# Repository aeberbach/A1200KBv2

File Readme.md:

A few years ago I made my first Amiga 1200 mechanical keyboard. I did not know at the time about any other efforts that might be underway so I just went ahead and did it. It turned out well and a lot of people built them. Still, there is always a temptation to try and improve something. I was never really happy about the mounting system and the 9U spacebar was a problem, even more so than finding the keycaps that match the Amiga key sizes because modern keyboards went in a different direction.

So here is version 2. At the time of the last keyboard, low-profile keyswitches existed but were hard to find and often could not use MX-stem caps, now it is easier. I'm typing this with a Nuphy Air75 v2 with "Gateron x Nuphy Moss" KS-33 switches and the feel is amazing. There is a lighter variant "Wisteria" and a regular brown tactile option. Blue (clicky) and several variants of linear including red are available too. These switches use a different footprint to standard MX so the PCB had to be redone.

The low profile switches do not come in a 5-pin PCB mount version so a plate is essential. While laser-cut would be amazing I don't have a laser cutter, also that would not be 3-dimensional and would not leave space for the stabilizer wires. To keep it printable on common 3D printers there are multiple pieces to print. I have used eSun matte PLA, a good opaque material that is a good match for an A1200.net case in white or black. The stabilizers mount to the plates, the holes in the PCB underneath are only for clearance. These plates keep the keyswitches perfectly straight during assembly, improve keyboard stiffness, dampen sound and make for a better appearance.

Under the old keyboard a 10x3mm aluminium bar was used to stiffen the whole assembly, running from one side of the case to another sitting on 3d-printed mounts. I want to move that out of the way of expansions under the keyboard. I never noticed a problem with a TF1230 but with a larger accelerator having a heatsink it might be. There is plenty of room for a PiStorm32-lite, by far the fastest and most cost-effective accelerator today.

One thing that hasn't been done is to source a Caps Lock key with a window for the LED. The LED mount is still there and you can put a LED under the switch but I don't know where you can get a windowed keycap for it. The LED section of this keyboard includes a circuit where it will light an alternate LED for power when Caps Lock is active. My keybaord has a green LED for power but that changes to blue when Caps Lock is activated.

If you don't want to use the LED function of this keyboard you can just snip away the top right of the PCB and use the original Amiga 1200 LED PCB. In that case don't bother with LEDs, capacitor, resistors or the inverter chip.

Requirements:
- one PCB (see the 'fab' folder for gerber files, ready to build)
- 96 Gateron KS-33 keyswitches
- 5 Gateron 2U plate-mount low-profile stabilizers
- 1 more Gateron low-profile stabilizer to disassemble - bend your own wire from 1.0mm music wire, available from hobby stores.
- 0805 LEDs: red, green, yellow/orange and blue (or whatever colors you like for the various functions)
- 0805 current-limiting resistor for each LED. Choose a value not less than 300 ohms. If your LEDs are too bright you can use higher values. I found that 500-1k ohms is fine. Your LEDs may vary.
- 0.1uF 0805 decoupling capacitor
- SN74LVC2G04DBVR dual inverter (available Mouser electronics)
- 5-pin dupont housing, pins and ribbon cable to connect LED section to Amiga
- one FFC connector, 32-way RA 1.25mm pitch. Molex 52044-3245 (available Mouser Electronics) or look on AliExpress.
- one FFC ribbon cable, 31-way. Cut one connector from Molex 15168-0400 (available Mouser Electronics) or look on AliExpress.
- Printed left and right plates to house stabilizers and switches on top of PCB (STLs in 3dprint folder)
- Printed left, right and bottom mounts to secure the keyboard in your case (STLs in 3dprint folder)
- various M3 bolts or plastic rivets for assembly
- 96 Amiga keycaps: user Steveed on Amibay recently sorted this out with Signature Plastics and they are perfect. Seems expensive? Not until you spend hours looking for and buying various sets and never end up with a full set. 
 
The cost of all this varies with the cost of PCB manufacture, keyswitches and stabilizers and of course the keycaps. As a very rough guide expect to pay *no less* than about:
- PCB $20
- keyswitches $40
- stabilizers $20
- LEDs and other components $2
- FFC connector and cable $8
- 3D printed parts $10

And assembly will take at least three hours. That's just under $100 in parts alone and does not even count a quality set of keycaps at around $150. (But if you weren't slightly obsessed you probably wouldn't have an Amiga in 2024.)

The license for this keyboard is non-commercial. However if a person has ordered the minimum of 5 PCBs from one of the usual places and wants to offer the extras for sale at near cost that is reasonable.

Thanks to Steveed (Amibay) and to everyone that has supported this project. 

License: CC-BY-NC-SA 4.0

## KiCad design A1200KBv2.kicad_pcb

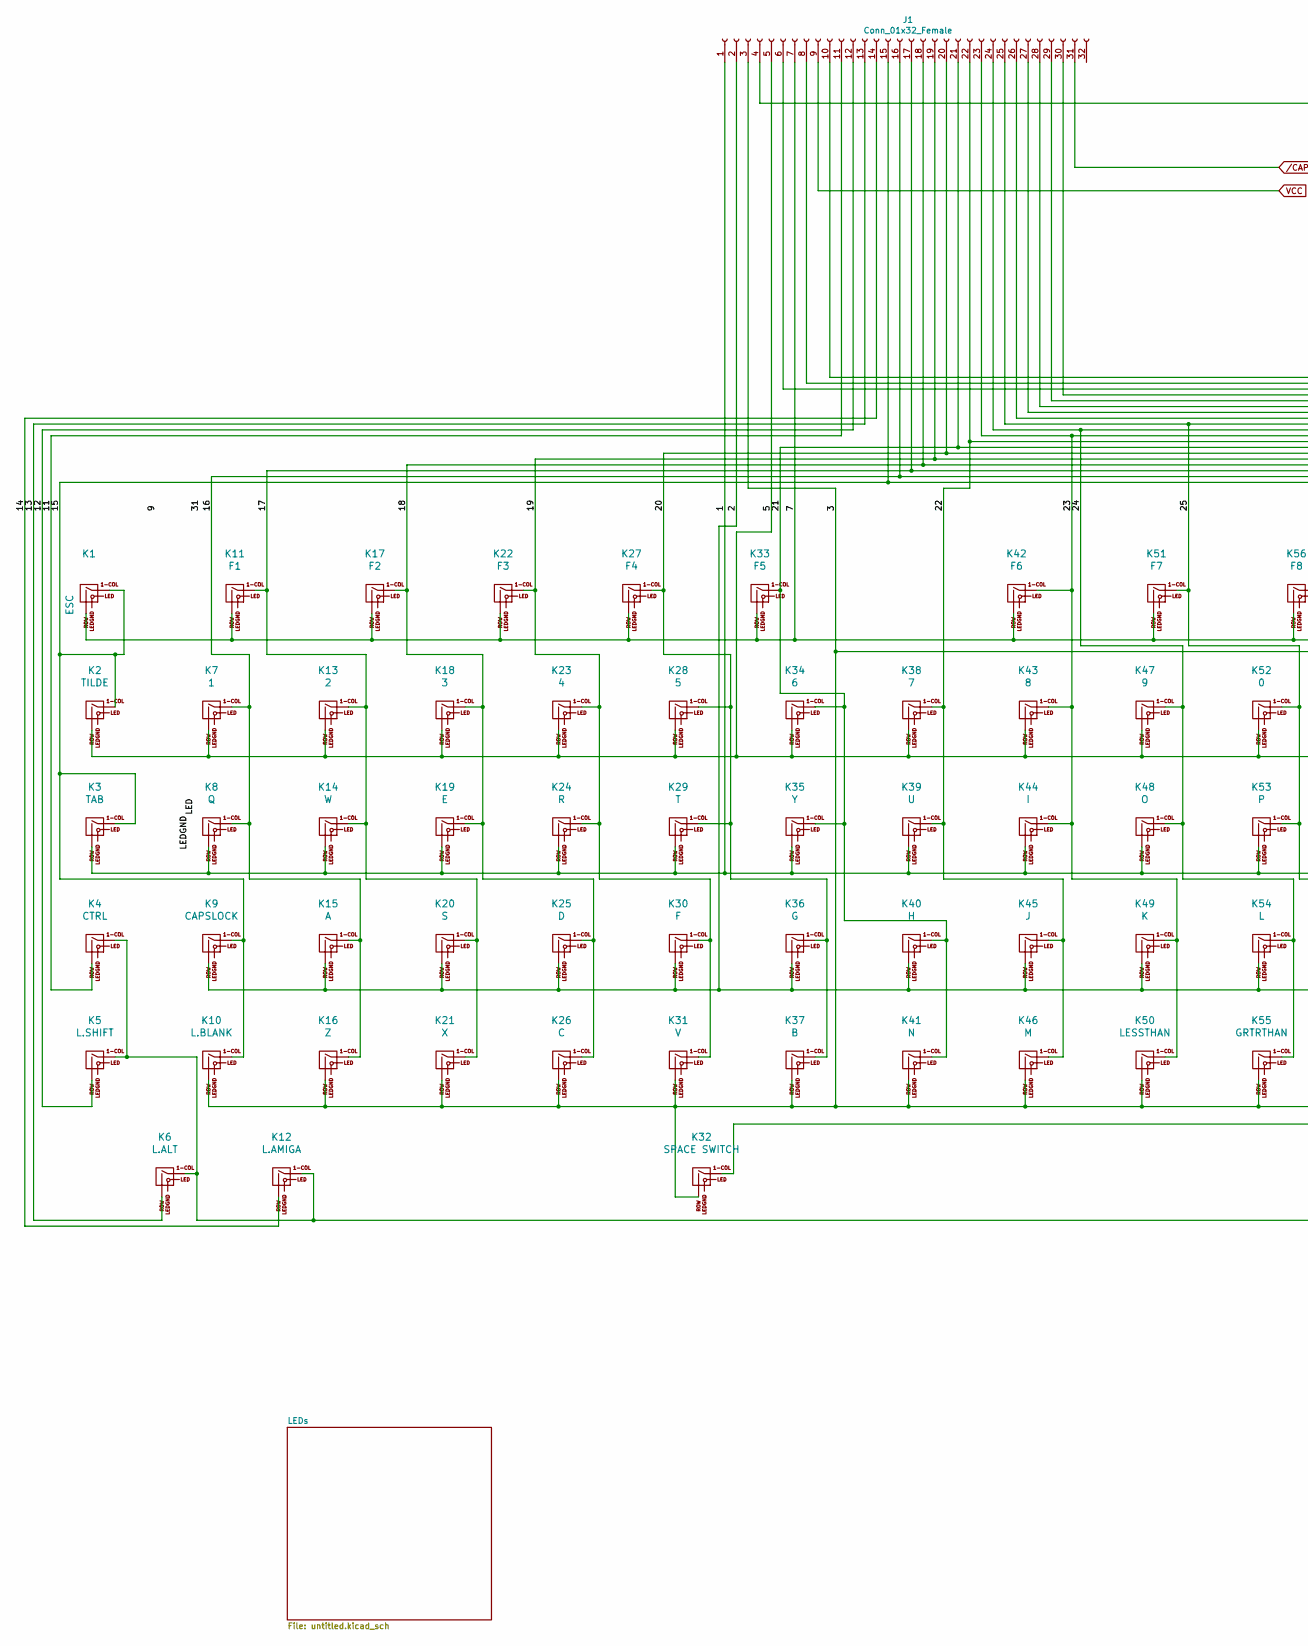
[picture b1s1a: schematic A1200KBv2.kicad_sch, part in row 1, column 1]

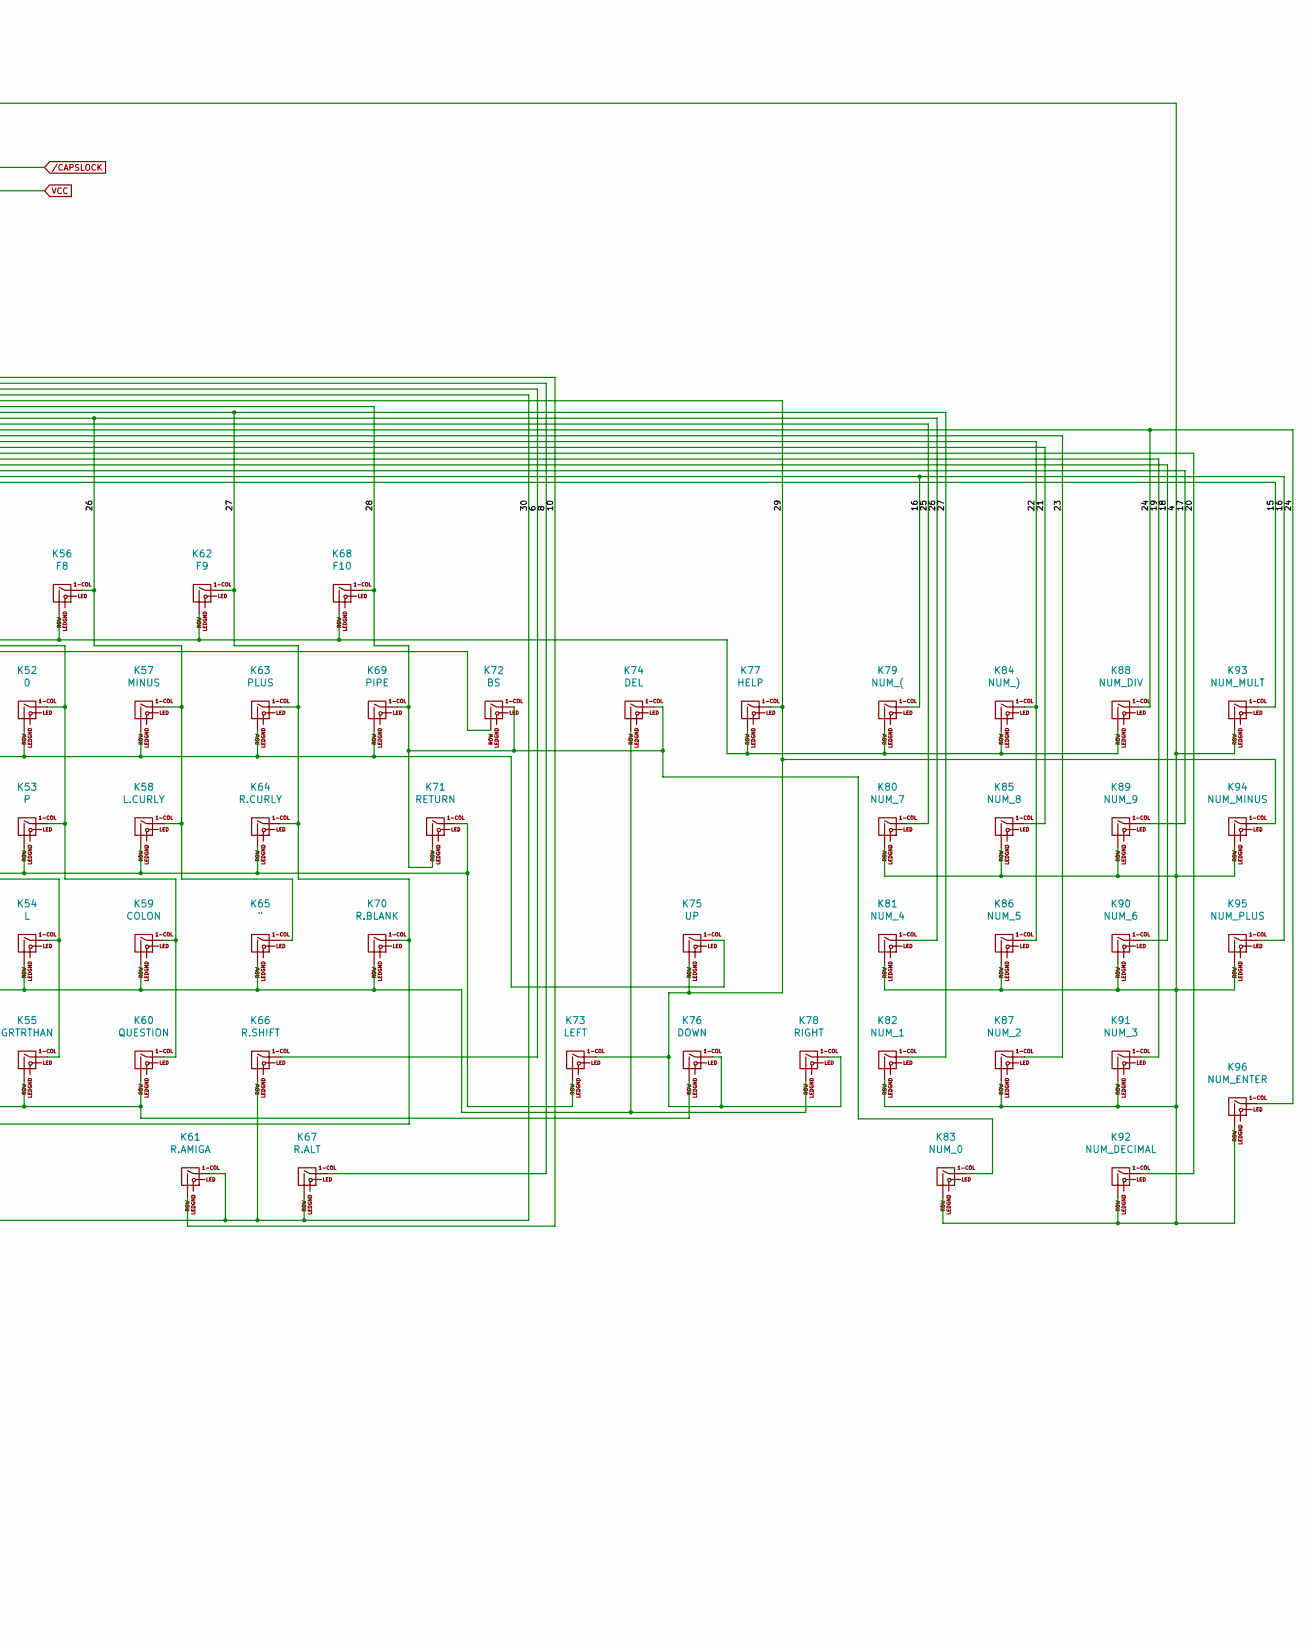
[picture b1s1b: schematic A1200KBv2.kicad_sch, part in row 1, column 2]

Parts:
J1: Conn_01x32_Female; FFC-1.25mm-RA-5204403245
K1: ESC; Gateron-KS33-Solderable-1U
K2: TILDE; Gateron-KS33-Solderable-1.5U
K3: TAB; KS-33-2U-stabilizer
K4: CTRL; Gateron-KS33-Solderable-1.25U
K5: L.SHIFT; Gateron-KS33-Solderable-1.75U
K6: L.ALT; Gateron-KS33-Solderable-1.25U
K7: 1; Gateron-KS33-Solderable-1U
K8: Q; Gateron-KS33-Solderable-1U
K9: CAPSLOCK; Gateron-KS33-Solderable-1U
K10: L.BLANK; Gateron-KS33-Solderable-1U
K11: F1; Gateron-KS33-Solderable-1.25U
K12: L.AMIGA; Gateron-KS33-Solderable-1.25U
K13: 2; Gateron-KS33-Solderable-1U
K14: W; Gateron-KS33-Solderable-1U
K15: A; Gateron-KS33-Solderable-1U
K16: Z; Gateron-KS33-Solderable-1U
K17: F2; Gateron-KS33-Solderable-1.25U
K18: 3; Gateron-KS33-Solderable-1U
K19: E; Gateron-KS33-Solderable-1U
K20: S; Gateron-KS33-Solderable-1U
K21: X; Gateron-KS33-Solderable-1U
K22: F3; Gateron-KS33-Solderable-1.25U
K23: 4; Gateron-KS33-Solderable-1U
K24: R; Gateron-KS33-Solderable-1U
K25: D; Gateron-KS33-Solderable-1U
K26: C; Gateron-KS33-Solderable-1U
K27: F4; Gateron-KS33-Solderable-1.25U
K28: 5; Gateron-KS33-Solderable-1U
K29: T; Gateron-KS33-Solderable-1U
K30: F; Gateron-KS33-Solderable-1U
K31: V; Gateron-KS33-Solderable-1U
K32: SPACE SWITCH; KS-33-8U-space
K33: F5; Gateron-KS33-Solderable-1.25U
K34: 6; Gateron-KS33-Solderable-1U
K35: Y; Gateron-KS33-Solderable-1U
K36: G; Gateron-KS33-Solderable-1U
K37: B; Gateron-KS33-Solderable-1U
K38: 7; Gateron-KS33-Solderable-1U
K39: U; Gateron-KS33-Solderable-1U
K40: H; Gateron-KS33-Solderable-1U
K41: N; Gateron-KS33-Solderable-1U
K42: F6; Gateron-KS33-Solderable-1.25U
K43: 8; Gateron-KS33-Solderable-1U
K44: I; Gateron-KS33-Solderable-1U
K45: J; Gateron-KS33-Solderable-1U
K46: M; Gateron-KS33-Solderable-1U
K47: 9; Gateron-KS33-Solderable-1U
K48: O; Gateron-KS33-Solderable-1U
K49: K; Gateron-KS33-Solderable-1U
K50: LESSTHAN; Gateron-KS33-Solderable-1U
K51: F7; Gateron-KS33-Solderable-1.25U
K52: 0; Gateron-KS33-Solderable-1U
K53: P; Gateron-KS33-Solderable-1U
K54: L; Gateron-KS33-Solderable-1U
K55: GRTRTHAN; Gateron-KS33-Solderable-1U
K56: F8; Gateron-KS33-Solderable-1.25U
K57: MINUS; Gateron-KS33-Solderable-1U
K58: L.CURLY; Gateron-KS33-Solderable-1U
K59: COLON; Gateron-KS33-Solderable-1U
K60: QUESTION; Gateron-KS33-Solderable-1U
K61: R.AMIGA; Gateron-KS33-Solderable-1.25U
K62: F9; Gateron-KS33-Solderable-1.25U
K63: PLUS; Gateron-KS33-Solderable-1U
K64: R.CURLY; Gateron-KS33-Solderable-1U
K65: "; Gateron-KS33-Solderable-1U
K66: R.SHIFT; KS-33-2U-stabilizer
K67: R.ALT; Gateron-KS33-Solderable-1.25U
K68: F10; Gateron-KS33-Solderable-1.25U
K69: PIPE; Gateron-KS33-Solderable-1U
K70: R.BLANK; Gateron-KS33-Solderable-1U
K71: RETURN; KS-33-ISO-2U-stabilizer
K72: BS; Gateron-KS33-Solderable-1U
K73: LEFT; Gateron-KS33-Solderable-1U
K74: DEL; Gateron-KS33-Solderable-1.5U
K75: UP; Gateron-KS33-Solderable-1U
K76: DOWN; Gateron-KS33-Solderable-1U
K77: HELP; Gateron-KS33-Solderable-1.5U
K78: RIGHT; Gateron-KS33-Solderable-1U
K79: NUM_(; Gateron-KS33-Solderable-1U
K80: NUM_7; Gateron-KS33-Solderable-1U
K81: NUM_4; Gateron-KS33-Solderable-1U
K82: NUM_1; Gateron-KS33-Solderable-1U
K83: NUM_0; KS-33-2U-stabilizer
K84: NUM_); Gateron-KS33-Solderable-1U
K85: NUM_8; Gateron-KS33-Solderable-1U
K86: NUM_5; Gateron-KS33-Solderable-1U
K87: NUM_2; Gateron-KS33-Solderable-1U
K88: NUM_DIV; Gateron-KS33-Solderable-1U
K89: NUM_9; Gateron-KS33-Solderable-1U
K90: NUM_6; Gateron-KS33-Solderable-1U
K91: NUM_3; Gateron-KS33-Solderable-1U
K92: NUM_DECIMAL; Gateron-KS33-Solderable-1U
K93: NUM_MULT; Gateron-KS33-Solderable-1U
K94: NUM_MINUS; Gateron-KS33-Solderable-1U
K95: NUM_PLUS; Gateron-KS33-Solderable-1U
K96: NUM_ENTER; KS-33-2U-stabilizer

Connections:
/1: J1.1, K3.2 (ROW), K8.2 (ROW), K14.2 (ROW), K19.2 (ROW), K24.2 (ROW), K29.2 (ROW), K35.2 (ROW), K39.2 (ROW), K44.2 (ROW), K48.2 (ROW), K53.2 (ROW), K58.2 (ROW), K64.2 (ROW), K71.1 (COL), K73.2 (ROW)
/2: J1.2, K9.2 (ROW), K15.2 (ROW), K20.2 (ROW), K25.2 (ROW), K30.2 (ROW), K36.2 (ROW), K40.2 (ROW), K45.2 (ROW), K49.2 (ROW), K54.2 (ROW), K59.2 (ROW), K65.2 (ROW), K70.2 (ROW), K74.2 (ROW), K78.2 (ROW)
/3: J1.3, K10.2 (ROW), K16.2 (ROW), K21.2 (ROW), K26.2 (ROW), K31.2 (ROW), K32.2 (ROW), K37.2 (ROW), K41.2 (ROW), K46.2 (ROW), K50.2 (ROW), K55.2 (ROW), K60.2 (ROW), K72.2 (ROW), K76.2 (ROW)
/4: J1.4, K80.2 (ROW), K81.2 (ROW), K82.2 (ROW), K83.2 (ROW), K85.2 (ROW), K86.2 (ROW), K87.2 (ROW), K89.2 (ROW), K90.2 (ROW), K91.2 (ROW), K92.2 (ROW), K93.2 (ROW), K94.2 (ROW), K95.2 (ROW), K96.2 (ROW)
/5: J1.5, K2.2 (ROW), K7.2 (ROW), K13.2 (ROW), K18.2 (ROW), K23.2 (ROW), K28.2 (ROW), K34.2 (ROW), K38.2 (ROW), K43.2 (ROW), K47.2 (ROW), K52.2 (ROW), K57.2 (ROW), K63.2 (ROW), K69.2 (ROW), K75.1 (COL)
/6: J1.6, K66.1 (COL)
/7: J1.7, K1.2 (ROW), K11.2 (ROW), K17.2 (ROW), K22.2 (ROW), K27.2 (ROW), K33.2 (ROW), K42.2 (ROW), K51.2 (ROW), K56.2 (ROW), K62.2 (ROW), K68.2 (ROW), K77.2 (ROW), K79.2 (ROW), K84.2 (ROW), K88.2 (ROW)
/8: J1.8, K67.1 (COL)
/10: J1.10, K61.2 (ROW)
/11: J1.11, K4.2 (ROW)
/12: J1.12, K5.2 (ROW)
/13: J1.13, K6.2 (ROW)
/14: J1.14, K12.2 (ROW)
/15: J1.15, K1.1 (COL), K2.1 (COL), K3.1 (COL), K9.1 (COL), K10.1 (COL), K93.1 (COL)
/16: J1.16, K7.1 (COL), K8.1 (COL), K15.1 (COL), K16.1 (COL), K79.1 (COL), K95.1 (COL)
/17: J1.17, K11.1 (COL), K13.1 (COL), K14.1 (COL), K20.1 (COL), K21.1 (COL), K89.1 (COL)
/18: J1.18, K17.1 (COL), K18.1 (COL), K19.1 (COL), K25.1 (COL), K26.1 (COL), K90.1 (COL)
/19: J1.19, K22.1 (COL), K23.1 (COL), K24.1 (COL), K30.1 (COL), K31.1 (COL), K91.1 (COL)
/20: J1.20, K27.1 (COL), K28.1 (COL), K29.1 (COL), K36.1 (COL), K37.1 (COL), K92.1 (COL)
/21: J1.21, K33.1 (COL), K34.1 (COL), K35.1 (COL), K40.1 (COL), K41.1 (COL), K85.1 (COL)
/22: J1.22, K38.1 (COL), K39.1 (COL), K45.1 (COL), K46.1 (COL), K84.1 (COL), K86.1 (COL)
/23: J1.23, K42.1 (COL), K43.1 (COL), K44.1 (COL), K49.1 (COL), K50.1 (COL), K87.1 (COL)
/24: J1.24, K47.1 (COL), K48.1 (COL), K54.1 (COL), K55.1 (COL), K88.1 (COL), K96.1 (COL)
/25: J1.25, K51.1 (COL), K52.1 (COL), K53.1 (COL), K59.1 (COL), K60.1 (COL), K80.1 (COL)
/26: J1.26, K56.1 (COL), K57.1 (COL), K58.1 (COL), K65.1 (COL), K81.1 (COL)
/27: J1.27, K32.1 (COL), K62.1 (COL), K63.1 (COL), K64.1 (COL), K70.1 (COL), K82.1 (COL)
/28: J1.28, K68.1 (COL), K69.1 (COL), K71.2 (ROW), K72.1 (COL), K74.1 (COL), K83.1 (COL)
/29: J1.29, K73.1 (COL), K75.2 (ROW), K76.1 (COL), K77.1 (COL), K78.1 (COL), K94.1 (COL)
/30: J1.30, K4.1 (COL), K5.1 (COL), K6.1 (COL), K12.1 (COL), K61.1 (COL), K66.2 (ROW), K67.2 (ROW)
VCC: J1.9; also elsewhere on the board
/CAPSLOCK: J1.31; also elsewhere on the board

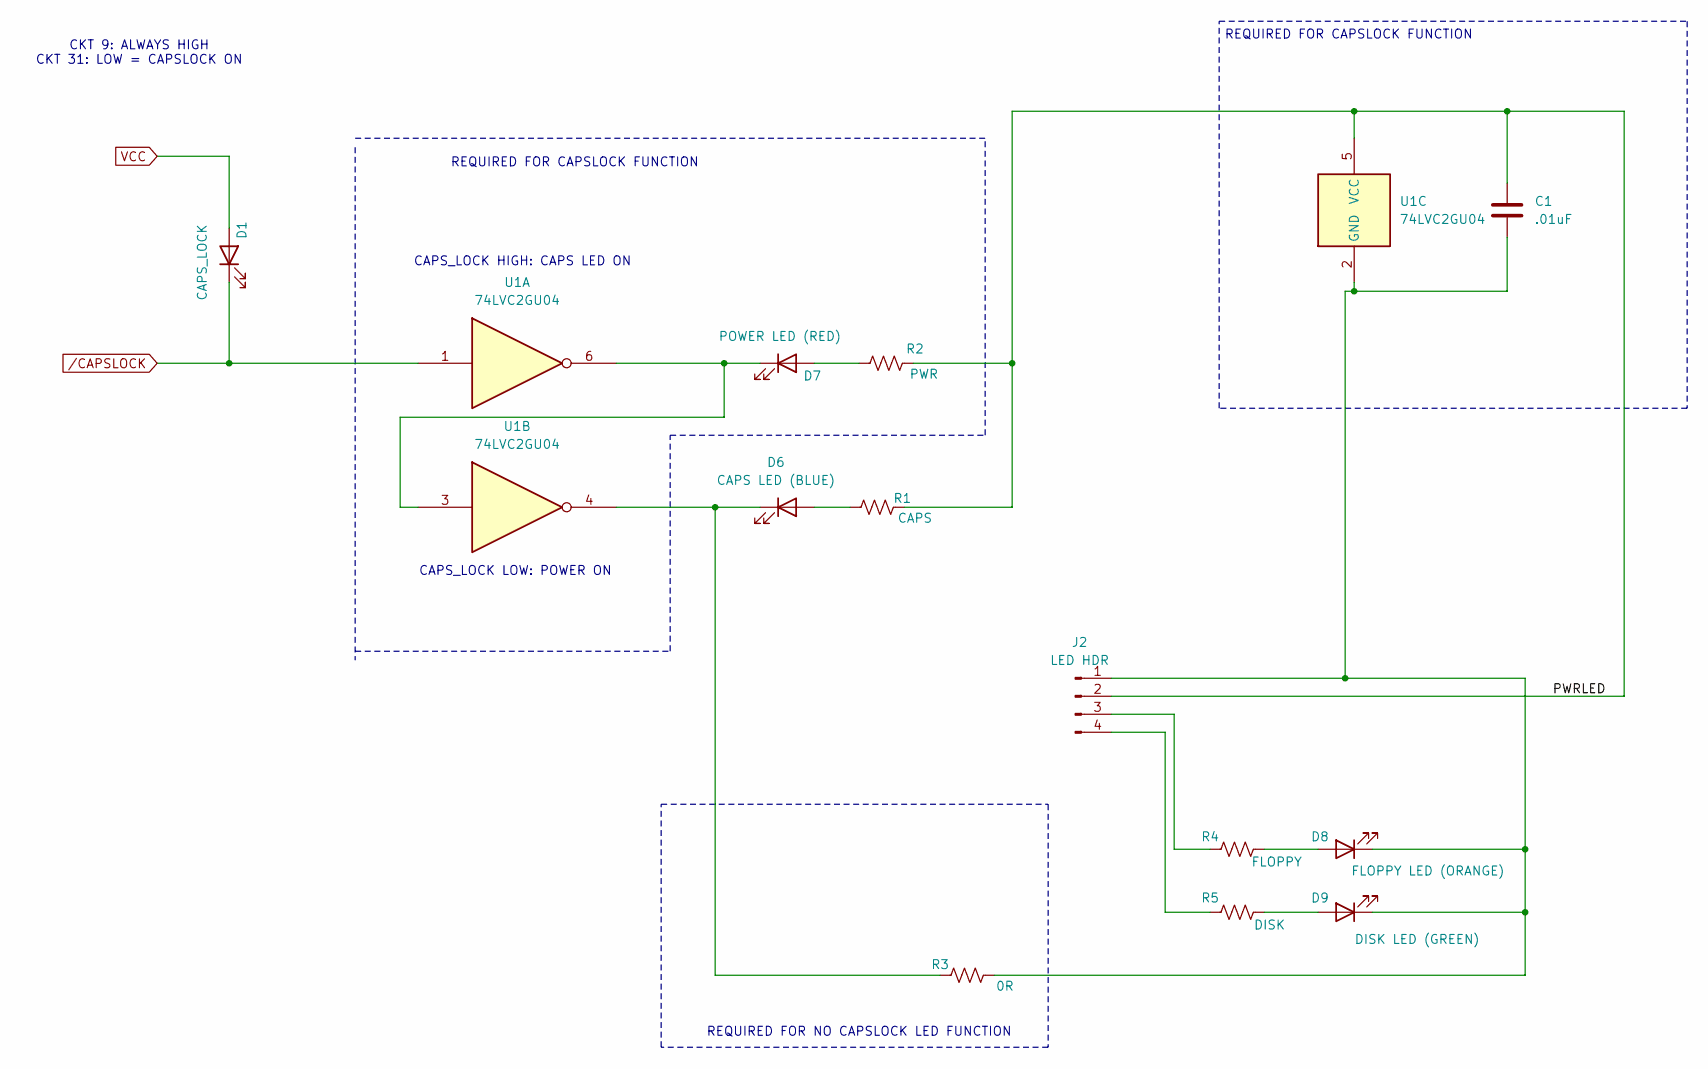
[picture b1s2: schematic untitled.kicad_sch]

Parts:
C1: .01uF; C_0805_2012Metric_Pad1.18x1.45mm_HandSolder
D1: CAPS_LOCK; LED_0805_2012Metric
D6: CAPS LED (BLUE); LED_0805_2012Metric
D7: POWER LED (RED); LED_0805_2012Metric
D8: FLOPPY LED (ORANGE); LED_0805_2012Metric
D9: DISK LED (GREEN); LED_0805_2012Metric
J2: LED HDR; PinHeader_1x04_P2.54mm_Vertical
R1: CAPS; R_0805_2012Metric_Pad1.20x1.40mm_HandSolder
R2: PWR; R_0805_2012Metric_Pad1.20x1.40mm_HandSolder
R3: 0R; R_0805_2012Metric_Pad1.20x1.40mm_HandSolder
R4: FLOPPY; R_0805_2012Metric_Pad1.20x1.40mm_HandSolder
R5: DISK; R_0805_2012Metric_Pad1.20x1.40mm_HandSolder
U1: 74LVC2GU04; SOT-23-6

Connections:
/LEDs/PWRLED: C1.1, J2.2, R1.2, R2.2, U1.5 (VCC)
unnamed: D6.2 (A), R1.1
unnamed: D6.1 (K), R3.1, U1.4
unnamed: D7.2 (A), R2.1
unnamed: D7.1 (K), U1.3, U1.6
unnamed: D8.2 (A), R4.2
unnamed: C1.2, D8.1 (K), D9.1 (K), J2.1, R3.2, U1.2 (GND)
unnamed: D9.2 (A), R5.2
unnamed: J2.3, R4.1
unnamed: J2.4, R5.1
VCC: D1.2 (A); also elsewhere on the board
/CAPSLOCK: D1.1 (K), U1.1; also elsewhere on the board

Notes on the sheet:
CAPS_LOCK LOW: POWER ON
CKT 9: ALWAYS HIGH CKT 31: LOW = CAPSLOCK ON
REQUIRED FOR CAPSLOCK FUNCTION
CAPS_LOCK HIGH: CAPS LED ON
REQUIRED FOR NO CAPSLOCK LED FUNCTION

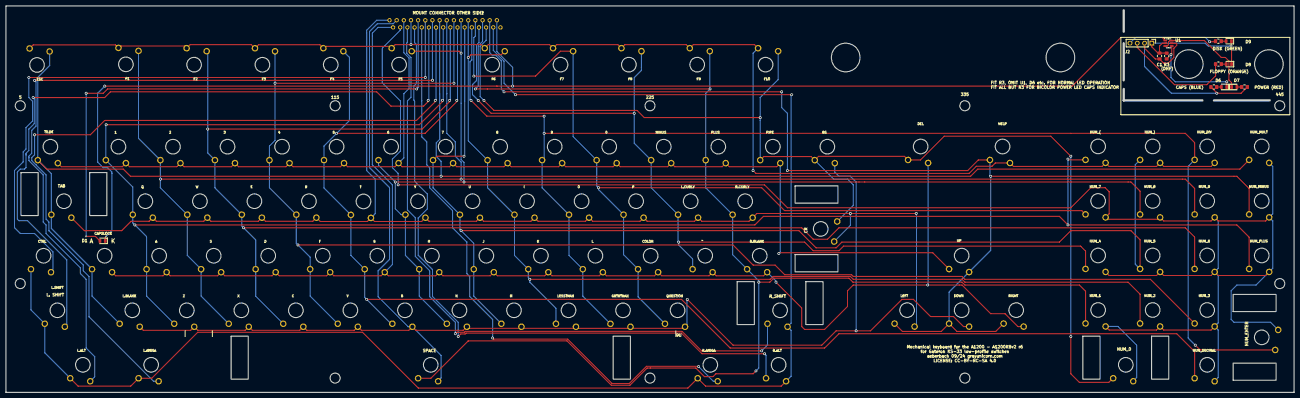
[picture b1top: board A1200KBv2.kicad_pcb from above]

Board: 2 copper layers, 450.0 x 135.0 mm, 110 parts (1 on the bottom side), 41 nets.

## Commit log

2024-06-20 rev 1 of new A1200kb for KS-33 switches
2024-06-20 license
2024-06-20 BM and estimated costs
2024-06-21 New version with new footprints; low-profile plate stabilizers
2024-07-08 fab 9/7/24 A1200 for KS-33 A1200.net case
2024-08-07 Current
2024-08-07 remove junk files
2024-08-07 arrange LEDs
2024-08-22 Plates for final r5
2024-08-27 Production
2024-09-02 10mm higher; keyboard connector out of the way
2024-09-02 Revert "10mm higher; keyboard connector out of the way"
    This reverts commit 7b7d121ea175ab04d54ee7bb06e71218aa1ce09d.
2024-09-02 v6 (keyboard connector out of the way, 135mm high)
2024-09-02 v6 as manufactured
2024-09-03 Move some parts into production folder
2024-09-13 in production V6
2024-09-13 r6 for FFC connector above F keys
2024-10-06 Revise right pate again - R. shift key smooth
2024-10-14 Consistent naming STL
2024-10-14 revise readme
2024-11-03 sort 3D print files
2025-01-12 A1200KBV2 reorg files and prod slicer files
2025-02-16 remove lower tabs on left and right mounts
2025-02-16 replace universal mnounts with dedicated for now
2025-02-16 Replace Commodore/A1200 left and right mounts in production folder
2025-03-10 no special changes
2026-04-10 Commit STEP
